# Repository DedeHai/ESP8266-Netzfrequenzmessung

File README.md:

# ESP8266-Netzfrequenzmessung
Measure 50Hz power grid frequency deviation using an ESP8266.

For discussions about this visit forum.netzsin.us

License:
Software under MIT license
Hardware under Creative Commons 4.0 license: CC-BY-NC-SA

#Mutatio Hardware

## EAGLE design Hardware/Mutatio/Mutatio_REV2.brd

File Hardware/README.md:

#Mutatio: grid frequency tracker
part of the netzsin.us project

 |

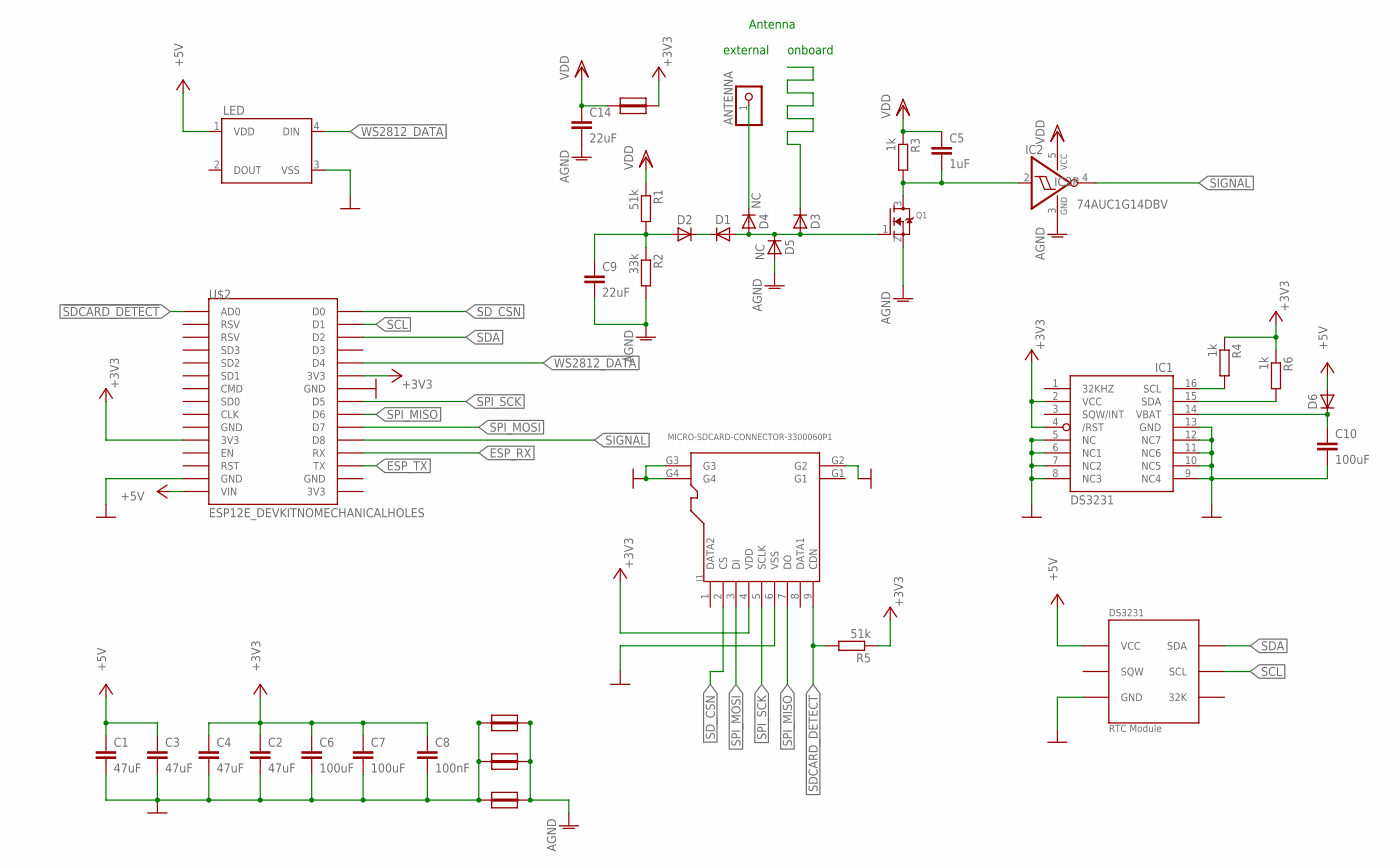
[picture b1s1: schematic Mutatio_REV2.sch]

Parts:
ANTENNA: PINHD-1X1CB; 1X01-CLEANBIG
C1, C2, C3, C4: 47uF; C0805
C5: 1uF; C0603
C6, C7, C10: 100uF; C1206
C8: 100nF; C0603
C9, C14: 22uF; C0603
D1, D2, D3, D6: DIODE-MINIMELF; MINIMELF
D4, D5: NC; MINIMELF
IC1: DS3231/SO; SO16W
IC2: 74AUC1G14DBV; SOT23-5
J1: MICRO-SDCARD-CONNECTOR-3300060P1; 9P-SMD-W-RING
LED: WS2812B
Q1: MOSFET-NREFLOW; SOT23
R1, R5: 51k; R0603
R2: 33k; R0603
R3, R4, R6: 1k; R0603
U$1: DS3231_MODULEBIG_CONNECTER_ONLY; DS3231_MODULE_BIGCON
U$2: ESP12E_DEVKITNOMECHANICALHOLES; ESP12E_DEVKIT_NOHOLES
U$7, U$8, U$9, U$10: SHORT

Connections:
!SDCARD_DETECT: J1.9 (CDN), R5.2, U$2.AD0
+3V3: C2.1, C4.1, C6.1, C7.1, C8.1, IC1.2 (VCC), IC1.4 (/RST), J1.4 (VDD), R4.1, R5.1, R6.1, U$2.3V3@0 (3V3), U$2.3V3@1 (3V3), U$7.P$2
+5V: C1.1, C3.1, D6.A, LED.1 (VDD), U$1.VCC@2 (VCC), U$2.VIN
AGND: C9.2, C14.2, D5.A, IC2.3 (GND), Q1.2 (S), R2.2, U$8.P$2, U$9.P$2, U$10.P$2
ANTENNA: D1.A, D3.A, D4.A, D5.C, Q1.1 (G)
BOARDANTENNA: D3.C
ESP_RX: U$2.RX
ESP_TX: U$2.TX
GND: C1.2, C2.2, C3.2, C4.2, C6.2, C7.2, C8.2, C10.2, IC1.5 (NC), IC1.6 (NC1), IC1.7 (NC2), IC1.8 (NC3), IC1.9 (NC4), IC1.10 (NC5), IC1.11 (NC6), IC1.12 (NC7), IC1.13 (GND), J1.6 (VSS), J1.G2, J1.G3, J1.G4, LED.3 (VSS), U$1.GND@2 (GND), U$2.GND@1 (GND), U$2.GND@2 (GND), U$8.P$1, U$9.P$1, U$10.P$1
unnamed: D1.C, D2.C
unnamed: ANTENNA.1, D4.C
unnamed: C5.2, IC2.2 (I), Q1.3 (D), R3.2
unnamed: C10.1, D6.C, IC1.14 (VBAT)
REF1: C9.1, D2.A, R1.2, R2.1
SCL: IC1.16 (SCL), R4.2, U$1.SCL@2 (SCL), U$2.D1
SDA: IC1.15 (SDA), R6.2, U$1.SDA@2 (SDA), U$2.D2
SD_CSN: J1.2 (CS), U$2.D0
SIGNAL: IC2.4 (O), U$2.D8
SPI_MISO: J1.7 (DO), U$2.D6
SPI_MOSI: J1.3 (DI), U$2.D7
SPI_SCK: J1.5 (SCLK), U$2.D5
VDD: C5.1, C14.1, IC2.5 (VCC), R1.1, R3.1, U$7.P$1
WS2812_DATA: LED.4 (DIN), U$2.D4

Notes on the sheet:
Antenna
onboard
external

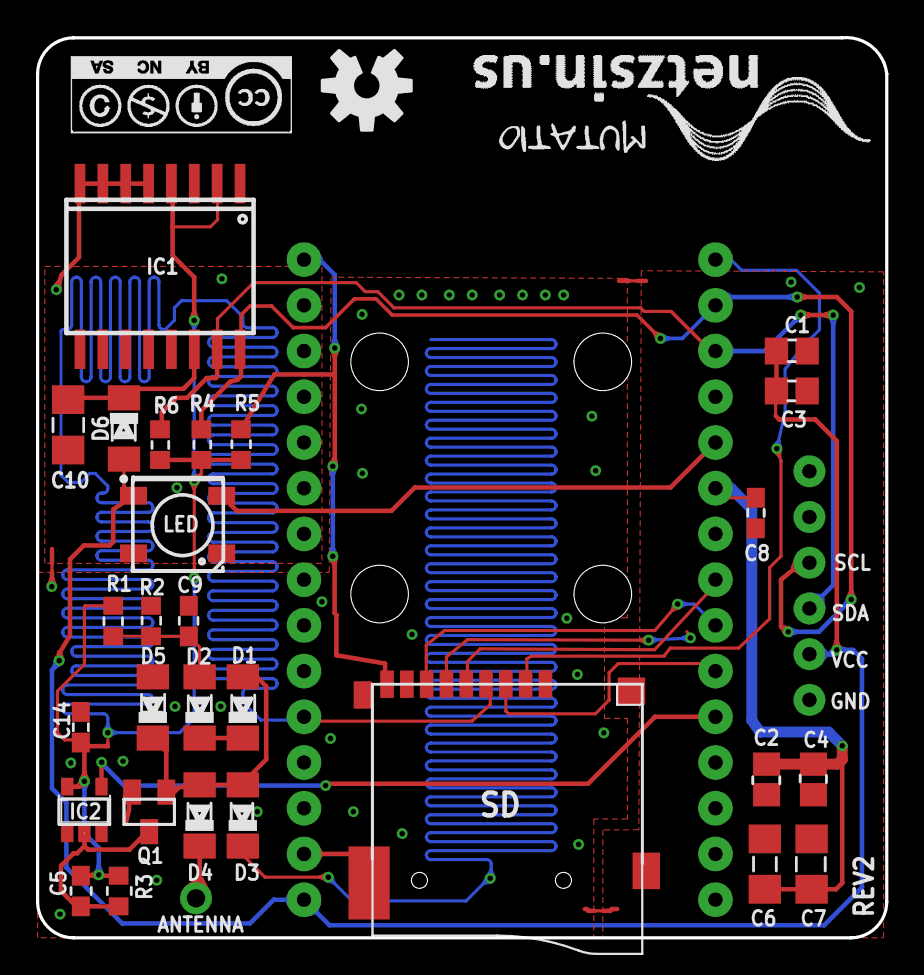
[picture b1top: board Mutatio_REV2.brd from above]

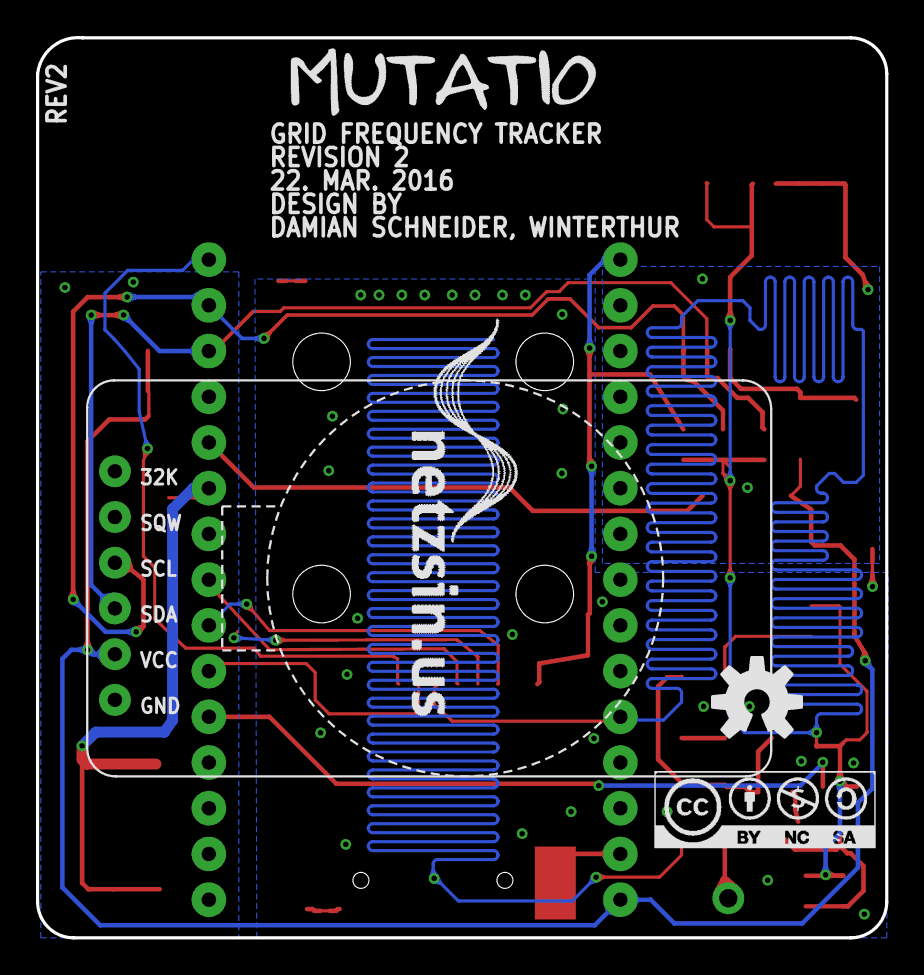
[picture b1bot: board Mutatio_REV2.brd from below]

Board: 2 copper layers, 47.2 x 50.0 mm, 39 parts (3 on the bottom side), 20 nets.

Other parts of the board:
U$3, U$6: OSHW-LOGO-M
U$4, U$5: CC-BY-NC-SA

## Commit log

2016-01-13 :circus_tent: Added .gitattributes
2016-01-13 Initial Release
    First release, basic functionality is implemented
2016-01-13 Add MIT license
2016-01-17 Added SD card, RGB LED and RTC support
    -SD card support added for saving measurement data
    -RGB led for status and frequency deviation
    -Real Time Clock to track time when server is not available (not very
    accurate yet, a bug?)
2016-01-17 Mutatio Hardware initial commit
    PCB design for the Mutatio hardware
2016-01-30 Big update, added LED, OTA update, changed noise detection algorithm, added RTC synchronization and server sync functionality
2016-01-30 added new config variable
2016-01-31 Added eeprom support for configuration Added a configuration webpage Added Accesppoint functionality fixed some bugs
2016-01-31 improvement in timekeeping accuracy
2016-01-31 changed webpage title
2016-01-31 addec cpu frequency to logfile, changed local log naming
2016-01-31 changed server json format and some other minor changes
2016-02-05 Added bug description and changed component values
2016-02-05 several bugfixes
2016-02-05 Add hardware photos
2016-02-05 Added BOM
2016-02-07 -commented out all the thingspeak test stuff -added sendout server configuration handling to functions and eeprom (address, port and URI) -handle config.sendAllData correctly -add non-DHCP control to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
2016-02-07 removed debug stuff
2016-02-09 bugfixes in LED and FCPU measurement
2016-02-12 bugfix in SD error blink and FCPU measurement
2016-02-12 Changed FCPU measurement method, added RTC measurement
2016-02-13 imageupload
2016-02-13 cosmetics
2016-02-13 removed debug line
2016-02-13 crop
2016-02-13 updated values and added comments
2016-02-19 bugfixes and improvements in plotly sending
2016-02-20 bugfix: cannot open the file too often, just reconnect the stream
2016-02-20 Added files via upload
2016-02-20 accepting more noise and higher dynamics, two values a second
2016-02-22 Improved plot.ly sending, added SD card readout to webpage
2016-02-24 bugfix: FCPU error computation error during RTC updat ;ASD:Q WçQEç&467#
2016-02-26 removed plotly
2016-02-26 removed plotly sendout
2016-03-04 Added User-Agent to header
2016-03-04 bugfix
2016-03-04 removed http from header
2016-03-05 minor bugfixes
2016-03-05 minor update
2016-03-06 changed number of captures
2016-03-11 bugfix in measurement overflow
2016-03-11 manually merged elhierro branch by adding a define
2016-03-12 added compiling info to serial output
2016-03-12 added python script to plot data from SD card
2016-03-19 error in BOM
2016-03-19 reformat
2016-03-21 working on REV2 board
2016-03-22 Revision2 work in progress
2016-03-25 finished revision 2
2016-03-30 increased API KEY max size
2016-04-03 Updated REV2 hardware
    changed the Signal and the LED pin so upload and bootup works properly

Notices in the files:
parts and their libraries:
SparkFun-LED: Licensing: Creative Commons ShareAlike 4.0 International - https://creativecommons.org/licenses/by-sa/4.0
